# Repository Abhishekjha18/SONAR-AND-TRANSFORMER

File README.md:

# SONAR-AND-TRANSFORMER
# Transformer & SONAR Project

This repository contains the design, simulation, fabrication, and testing of two analog circuit modules:
- **SONAR Module:** A narrowband ultrasonic Doppler sensor for motion detection.
- **Transformer Module:** Analog transformer circuits incorporating filters and voltage regulators for stable power delivery.

---

## SONAR Module

**Description:**
- Designed, simulated, fabricated, and tested a narrowband ultrasonic Doppler sensor for motion detection.
- Integrated transmitter and receiver circuits with ultrasonic sensors to enable accurate distance measurement.
- PCB layout was executed using **EagleCAD**.

**Key Technologies:**
- **LTSpice** for circuit simulation.
- **EagleCAD** for PCB design.
- Analog circuit design principles for sensor integration.
- **CIRCUITS THAT HELPED IN THE SONAR:**

---

## Transformer Module

**Description:**
- Developed analog transformer circuits that include essential filters and voltage regulators for reliable power delivery.
- Designed, simulated, fabricated, and tested the circuits to ensure stable performance under varying conditions.
- PCB layout was implemented using **KiCad**.

**Key Technologies:**
- **LTSpice** for circuit simulation.
- **KiCad** for PCB design.
- Analog circuit design best practices for power regulation.
- **CIRCUITS THAT HELPED IN THE TRANSFORMER:**

---

## Tools & Technologies

- **LTSpice:** Circuit simulation
- **EagleCAD:** PCB design for the SONAR module
- **KiCad:** PCB design for the Transformer module
- **Analog Circuit Design:** Implementation of filters, voltage regulators, rectifiers and sensor circuits

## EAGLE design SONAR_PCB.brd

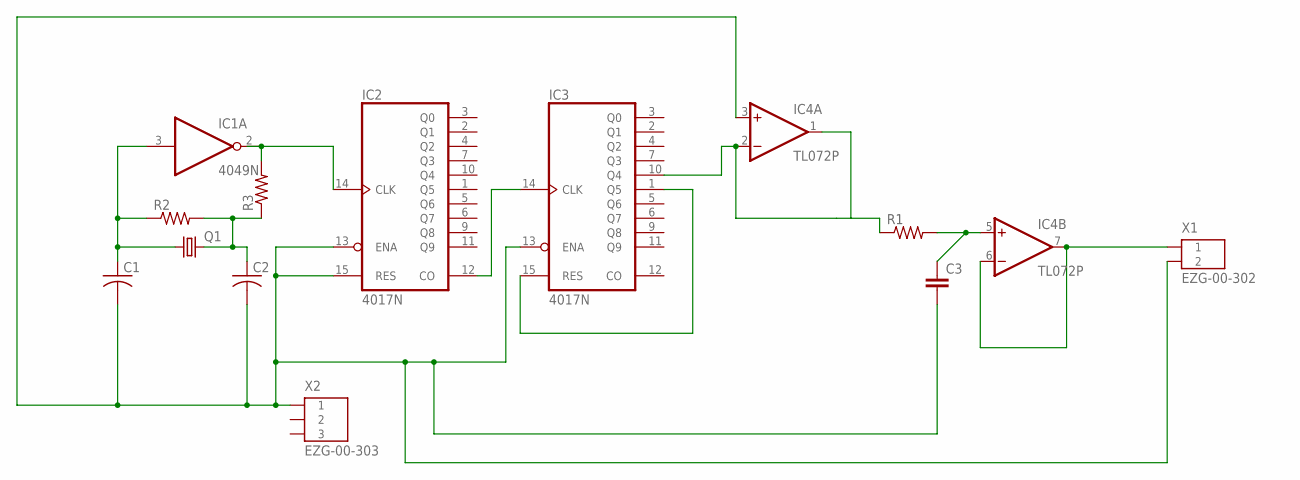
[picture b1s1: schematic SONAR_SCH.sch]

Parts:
C1, C2: C-US050-025X075; C050-025X075
C3: C2.5/2; C2.5-2
IC1: 4049N; DIL16
IC2, IC3: 4017N; DIL16
IC4: TL072P; DIL08
Q1: CRYSTALHC49U-V; HC49U-V
R1, R2, R3: R-US_0207/10; 0207/10
X1: EZG-00-302
X2: EZG-00-303

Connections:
unnamed: C1.1, IC1.3 (I), Q1.1, R2.1
unnamed: IC1.2 (O), IC2.14 (CLK), R3.2
unnamed: IC2.12 (CO), IC3.14 (CLK)
unnamed: IC3.10 (Q4), IC4.1 (OUT), IC4.2 (-IN), R1.1
unnamed: IC3.1 (Q5), IC3.15 (RES)
unnamed: C3.1, IC4.5 (+IN), R1.2
unnamed: IC4.6 (-IN), IC4.7 (OUT), X1.1
unnamed: C1.2, C2.2, C3.2, IC2.13 (ENA), IC2.15 (RES), IC3.13 (ENA), IC4.3 (+IN), X1.2, X2.1
unnamed: C2.1, Q1.2, R2.2, R3.1
V+: IC4.8 (V+)
V-: IC4.4 (V-)
VDD: IC1.1 (VDD), IC2.16 (VDD), IC3.16 (VDD)
VSS: IC1.8 (VSS), IC2.8 (VSS), IC3.8 (VSS)

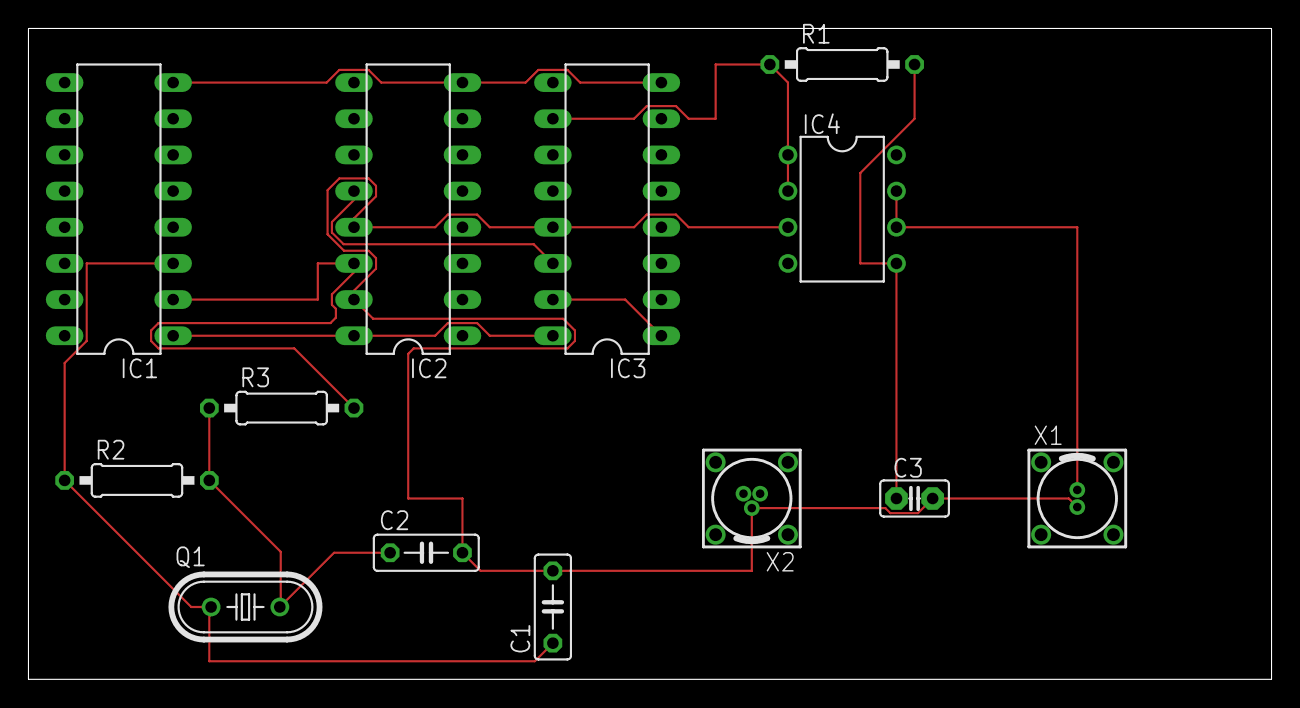
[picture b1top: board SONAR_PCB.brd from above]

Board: 2 copper layers, 87.3 x 45.7 mm, 13 parts (0 on the bottom side), 11 nets.

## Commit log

2025-02-09 Add files via upload
    THE CIR FILES OF THE CIRCUITS UTILISED DURING THE TRANSFORMER PROJECT
2025-02-09 Add files via upload
    sonar docs updated
